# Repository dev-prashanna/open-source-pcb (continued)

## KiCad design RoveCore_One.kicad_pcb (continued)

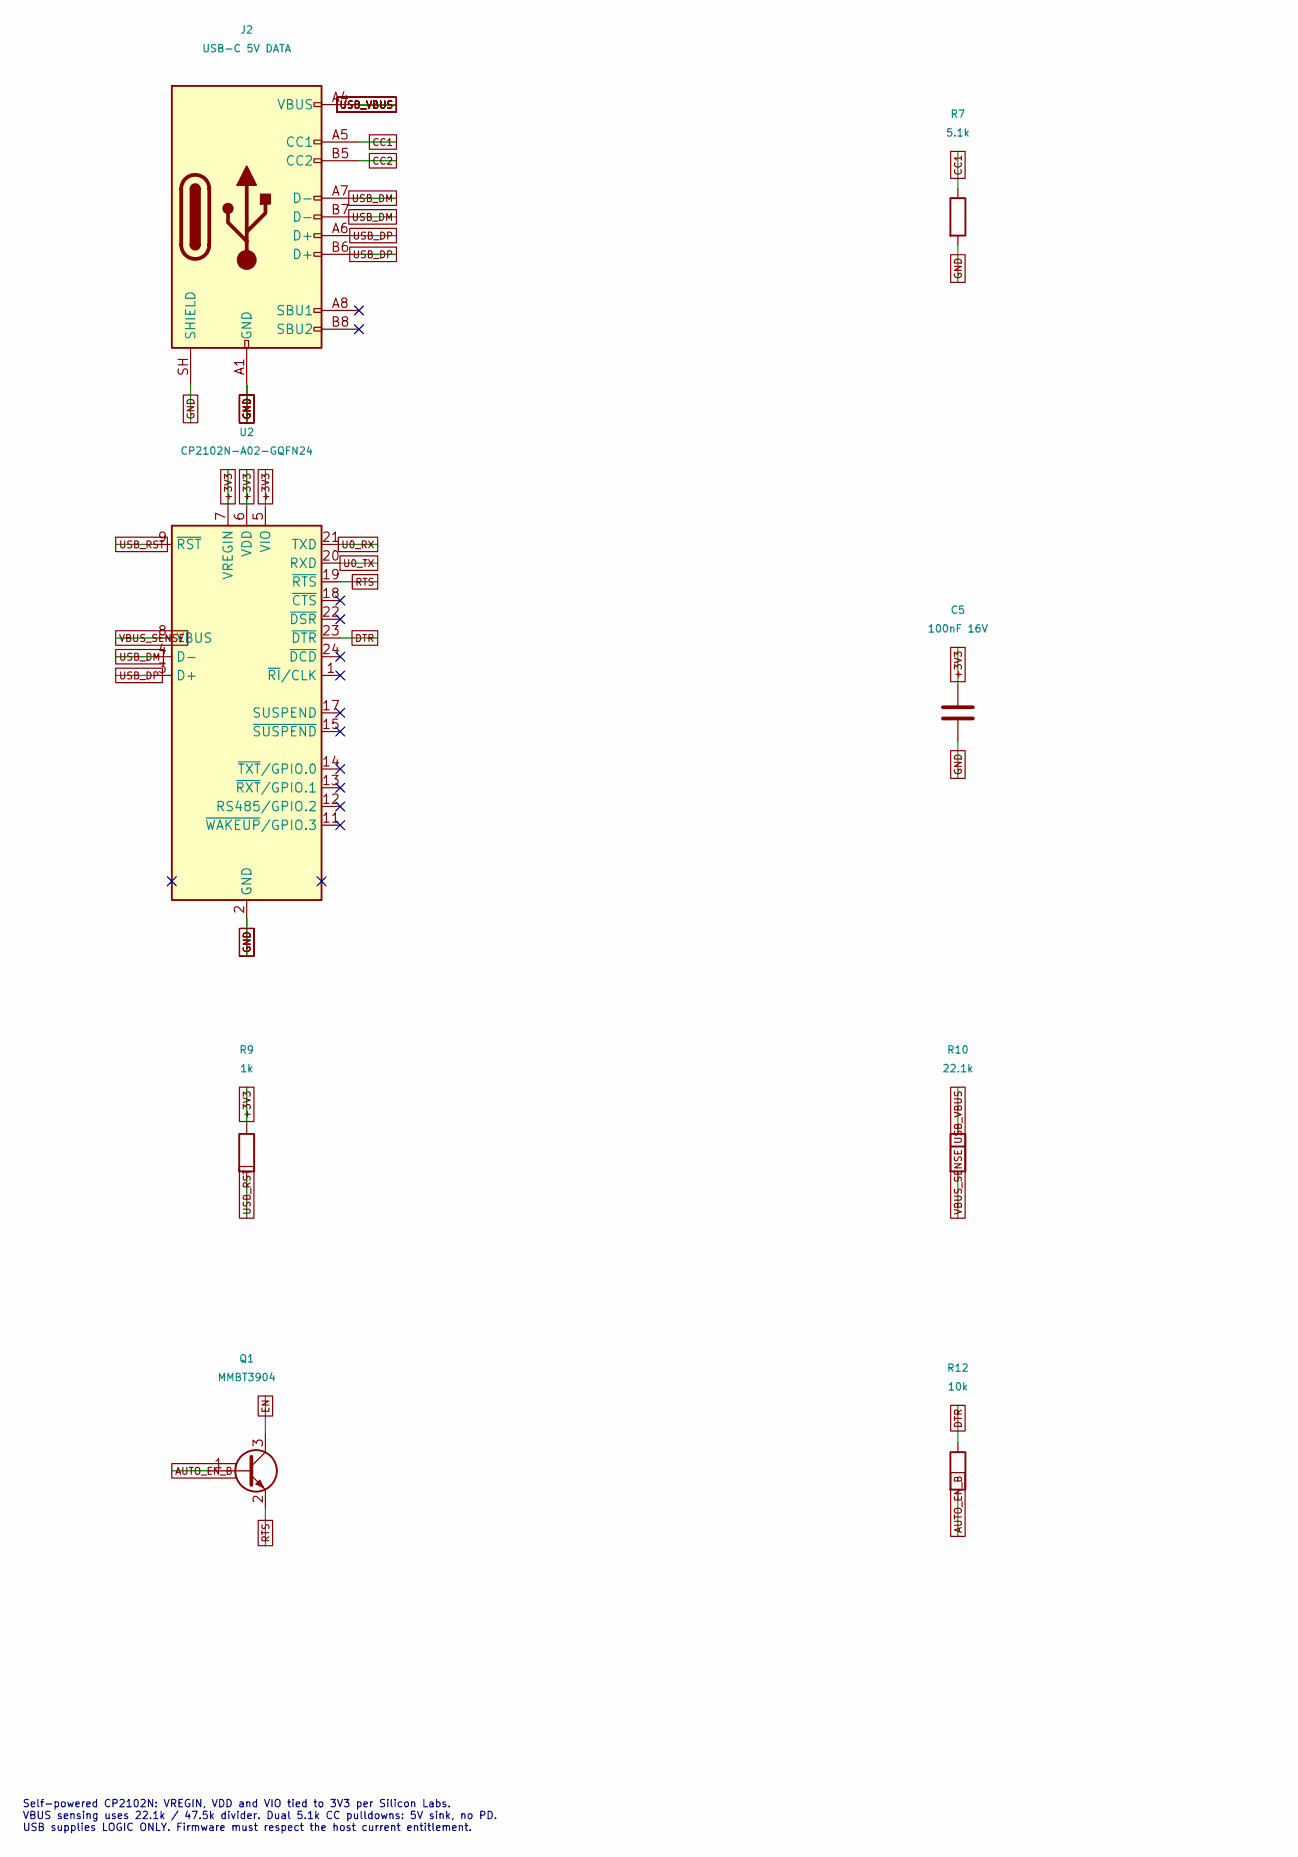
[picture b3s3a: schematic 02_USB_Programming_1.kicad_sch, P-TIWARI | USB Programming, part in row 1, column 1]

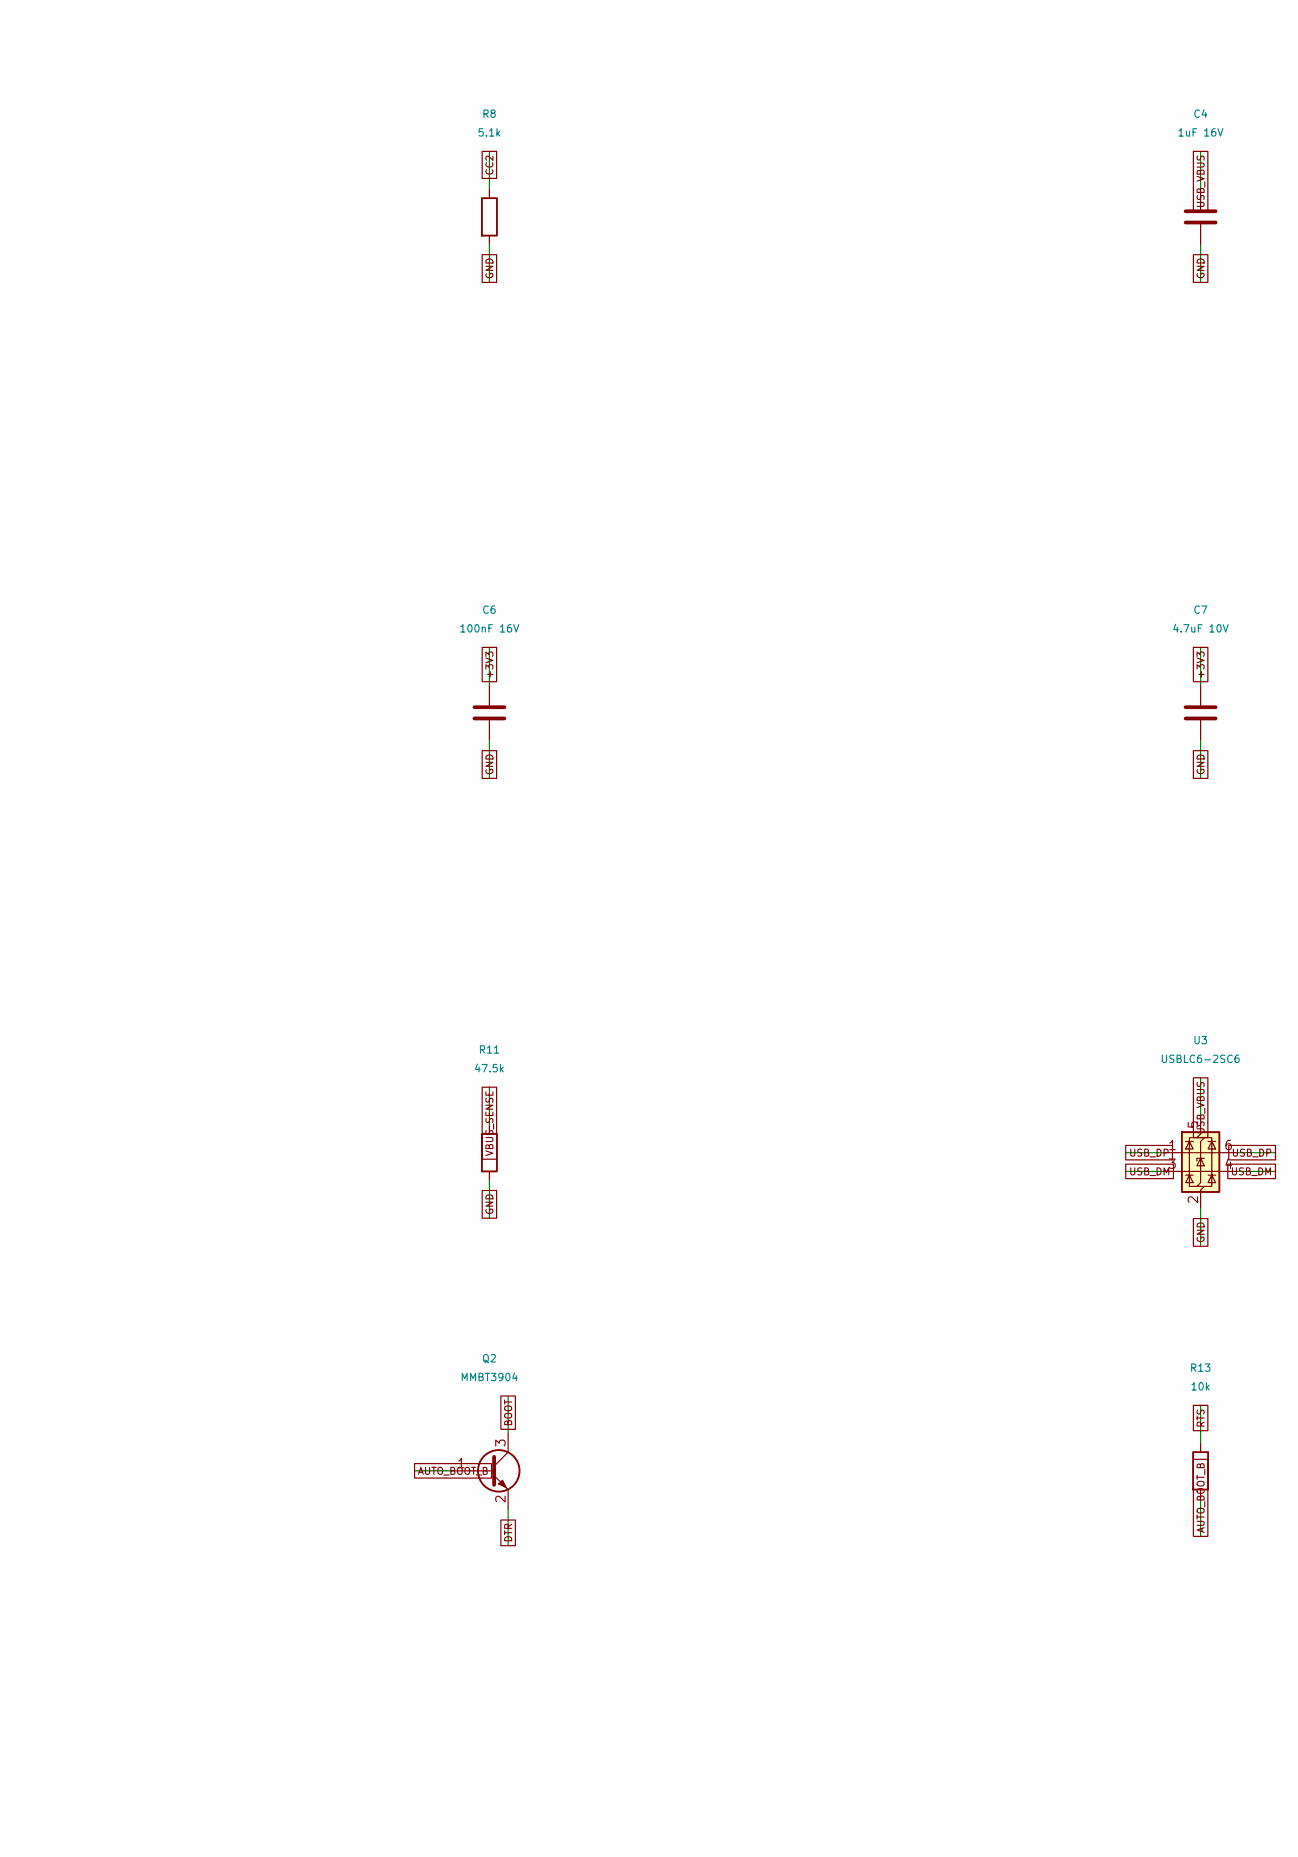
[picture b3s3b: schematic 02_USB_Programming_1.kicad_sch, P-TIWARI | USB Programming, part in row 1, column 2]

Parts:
C4: 1uF 16V; C_0603_1608Metric; MPN GRM188R61C105KA12D
C5, C6: 100nF 16V; C_0603_1608Metric; MPN GRM188R71C104KA01D
C7: 4.7uF 10V; C_0603_1608Metric; MPN GRM188R61A475KE15D
J2: USB-C 5V DATA; USB_C_Receptacle_HRO_TYPE-C-31-M-12; MPN TYPE-C-31-M-12
Q1, Q2: MMBT3904; SOT-23; MPN MMBT3904
R7, R8: 5.1k; R_0603_1608Metric; MPN RC0603FR-075K1L
R9: 1k; R_0603_1608Metric; MPN RC0603FR-071KL
R10: 22.1k; R_0603_1608Metric; MPN RC0603FR-0722K1L
R11: 47.5k; R_0603_1608Metric; MPN RC0603FR-0747K5L
R12, R13: 10k; R_0603_1608Metric; MPN RC0603FR-0710KL
U2: CP2102N-A02-GQFN24; QFN-24-1EP_4x4mm_P0.5mm_EP2.6x2.6mm; MPN CP2102N-A02-GQFN24
U3: USBLC6-2SC6; SOT-23-6; MPN USBLC6-2SC6

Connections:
+3V3: C5.1, C6.1, C7.1, R9.1, U2.5 (VIO), U2.6 (VDD), U2.7 (VREGIN); also elsewhere on the board
AUTO_BOOT_B: Q2.1 (B), R13.2
AUTO_EN_B: Q1.1 (B), R12.2
BOOT: Q2.3 (C); also elsewhere on the board
CC1: J2.A5 (CC1), R7.1
CC2: J2.B5 (CC2), R8.1
DTR: Q2.2 (E), R12.1, U2.23 (~DTR)
EN: Q1.3 (C); also elsewhere on the board
GND: C4.2, C5.2, C6.2, C7.2, J2.A1 (GND), J2.A12 (GND), J2.B1 (GND), J2.B12 (GND), J2.SH (SHIELD), R7.2, R8.2, R11.2, U2.2 (GND), U2.25 (GND), U3.2 (GND); also elsewhere on the board
RTS: Q1.2 (E), R13.1, U2.19 (~RTS)
U0_RX: U2.21 (TXD); also elsewhere on the board
U0_TX: U2.20 (RXD); also elsewhere on the board
USB_DM: J2.A7 (D-), J2.B7 (D-), U2.4 (D-), U3.3 (I/O2), U3.4 (I/O2)
USB_DP: J2.A6 (D+), J2.B6 (D+), U2.3 (D+), U3.1 (I/O1), U3.6 (I/O1)
USB_RST: R9.2, U2.9 (~RST)
USB_VBUS: C4.1, J2.A4 (VBUS), J2.A9 (VBUS), J2.B4 (VBUS), J2.B9 (VBUS), R10.1, U3.5 (VBUS); also elsewhere on the board
VBUS_SENSE: R10.2, R11.1, U2.8 (VBUS)

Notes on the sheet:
Self-powered CP2102N: VREGIN, VDD and VIO tied to 3V3 per Silicon Labs. VBUS sensing uses 22.1k / 47.5k divider. Dual 5.1k CC pulldowns: 5V sink, no PD. USB supplies LOGIC ONLY. Firmware must respect the host current entitlement.

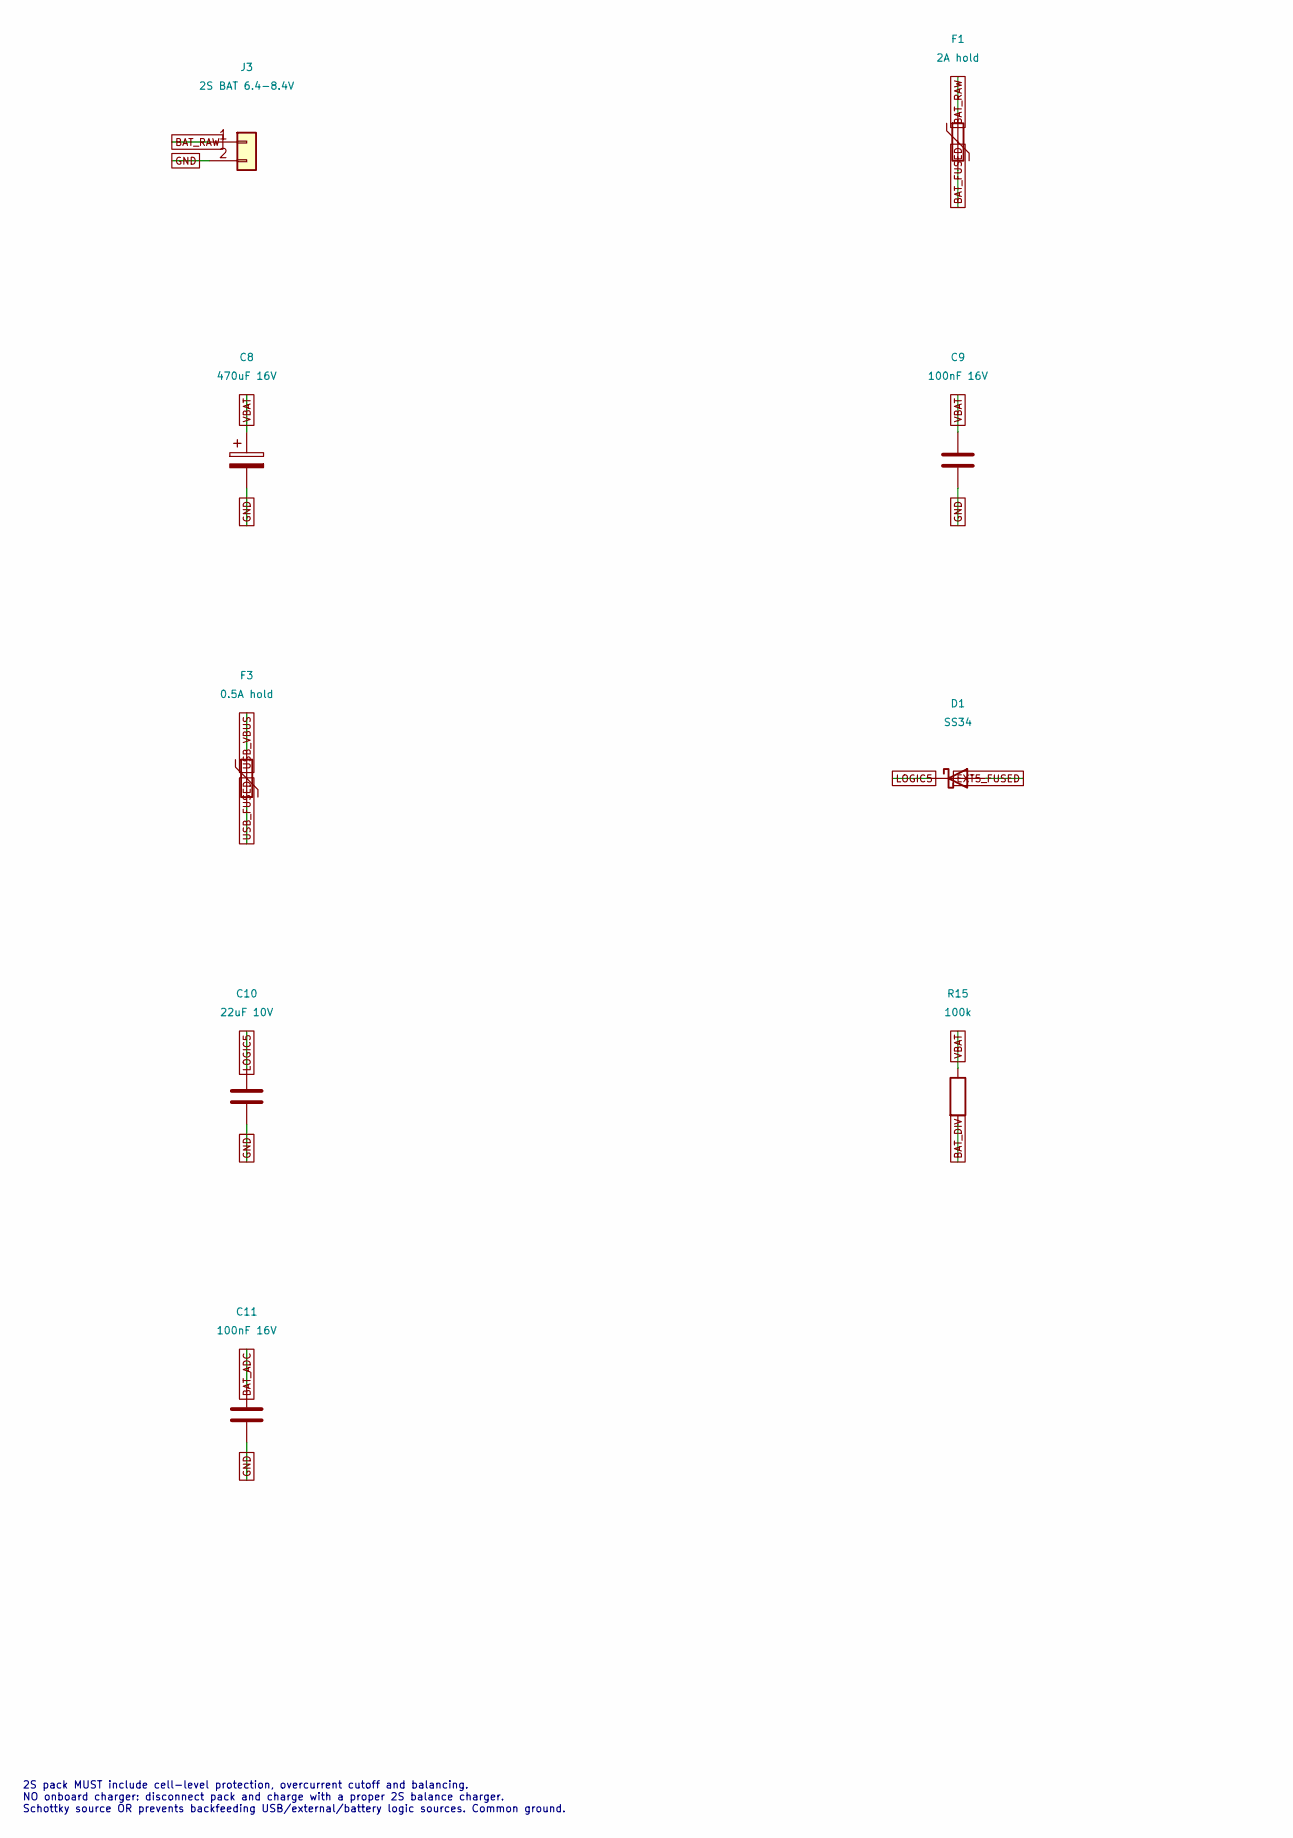
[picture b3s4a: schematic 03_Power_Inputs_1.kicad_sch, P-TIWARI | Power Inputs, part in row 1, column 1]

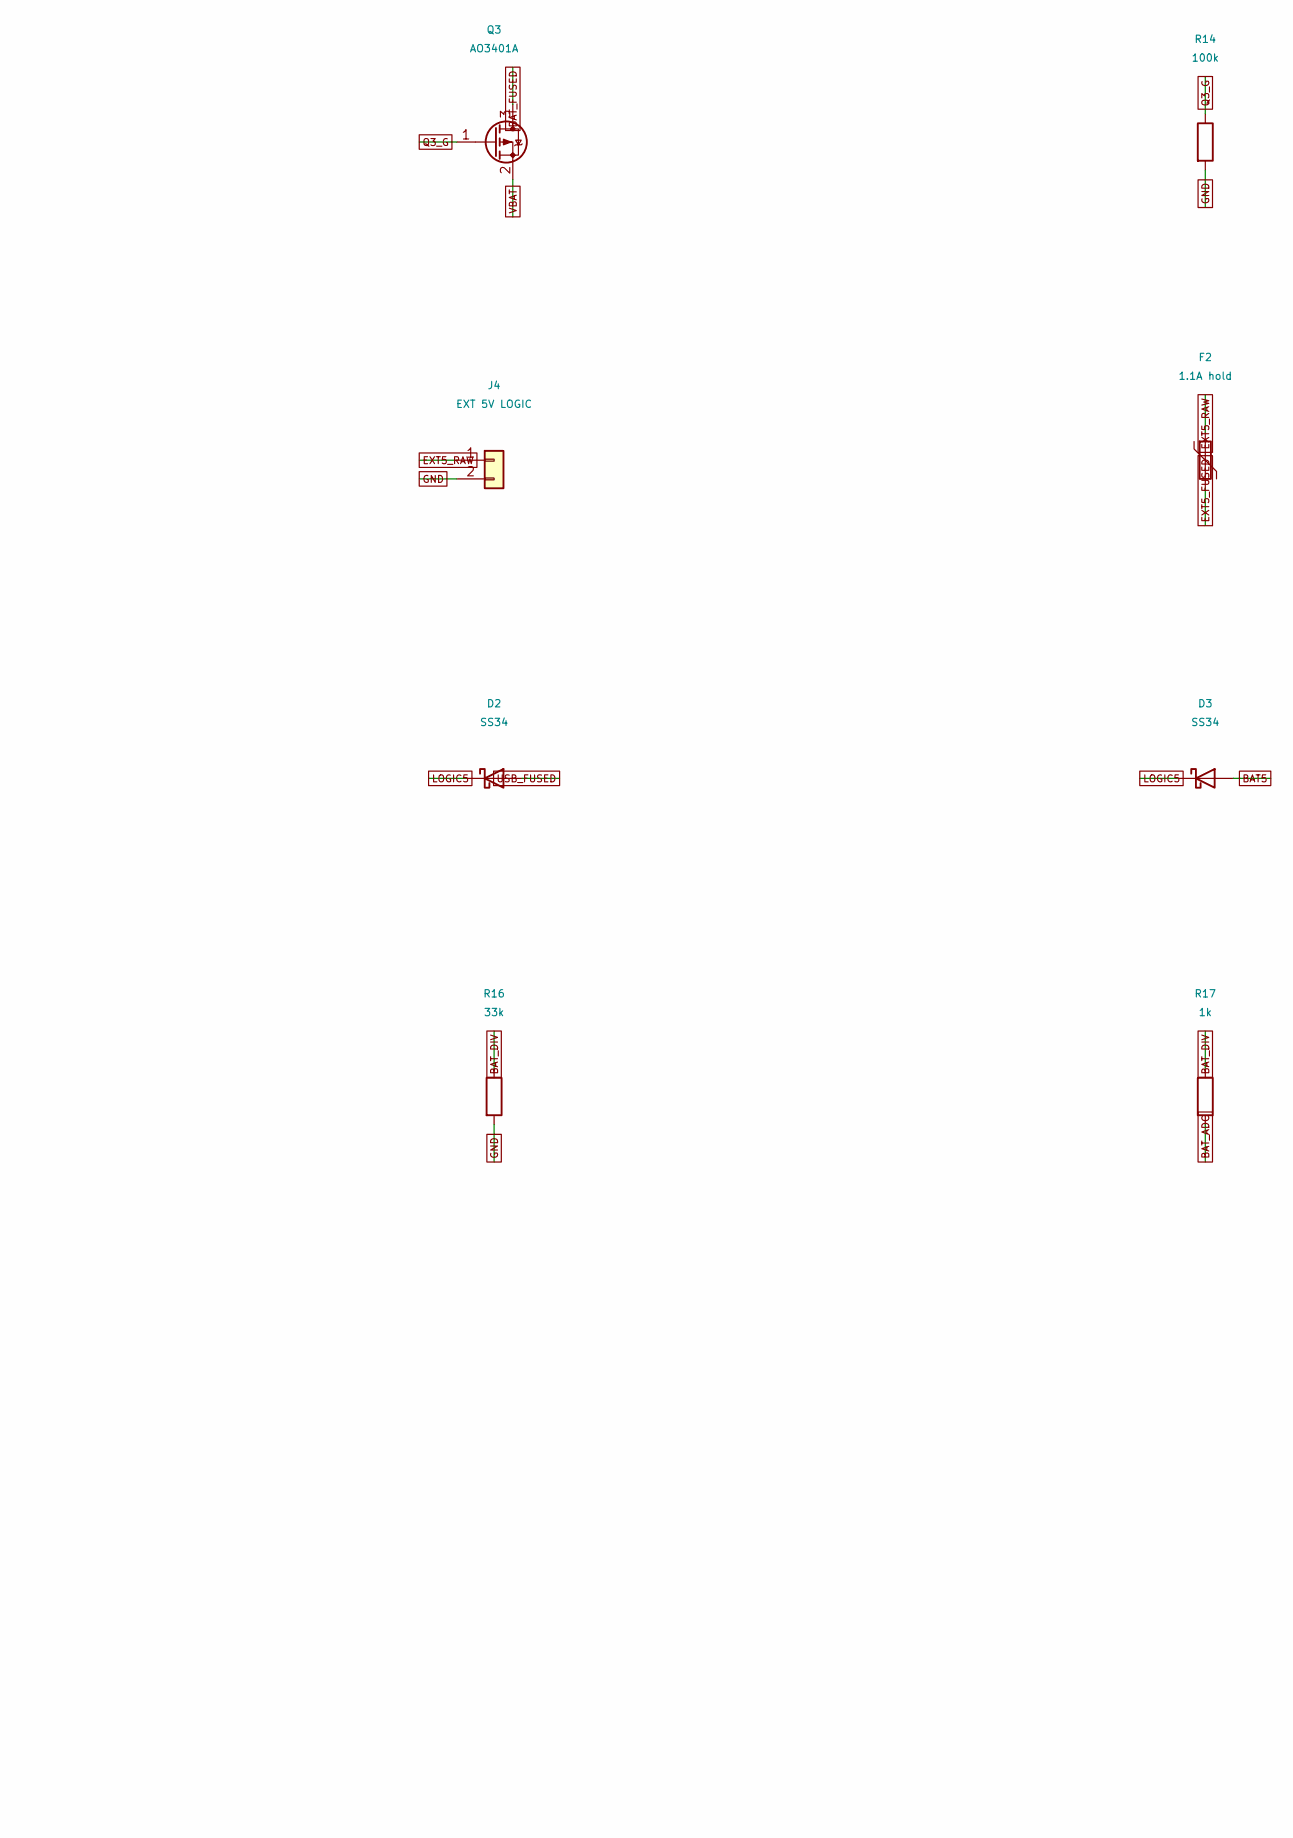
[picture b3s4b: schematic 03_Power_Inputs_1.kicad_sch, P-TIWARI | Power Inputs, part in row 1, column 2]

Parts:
C8: 470uF 16V; CP_Elec_8x10.5; MPN EEE-FK1C471P
C9, C11: 100nF 16V; C_0603_1608Metric; MPN GRM188R71C104KA01D
C10: 22uF 10V; C_0805_2012Metric; MPN GRM21BR61A226ME44L
D1, D2, D3: SS34; D_SMA; MPN SS34
F1: 2A hold; Fuse_1812_4532Metric; MPN 1812L200/16DR
F2: 1.1A hold; Fuse_1812_4532Metric; MPN 1812L110/16DR
F3: 0.5A hold; Fuse_1812_4532Metric; MPN 1812L050/24DR
J3: 2S BAT 6.4-8.4V; TerminalBlock_Phoenix_PT-1,5-2-3.5-H_1x02_P3.50mm_Horizontal; MPN 1984617
J4: EXT 5V LOGIC; TerminalBlock_Phoenix_PT-1,5-2-3.5-H_1x02_P3.50mm_Horizontal; MPN 1984617
Q3: AO3401A; SOT-23; MPN AO3401A
R14, R15: 100k; R_0603_1608Metric; MPN RC0603FR-07100KL
R16: 33k; R_0603_1608Metric; MPN RC0603FR-0733KL
R17: 1k; R_0603_1608Metric; MPN RC0603FR-071KL

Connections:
BAT5: D3.2 (A); also elsewhere on the board
BAT_ADC: C11.1, R17.2; also elsewhere on the board
BAT_DIV: R15.2, R16.1, R17.1
BAT_FUSED: F1.2, Q3.3 (D)
BAT_RAW: F1.1, J3.1
EXT5_FUSED: D1.2 (A), F2.2
EXT5_RAW: F2.1, J4.1
GND: C8.2, C9.2, C10.2, C11.2, J3.2, J4.2, R14.2, R16.2; also elsewhere on the board
LOGIC5: C10.1, D1.1 (K), D2.1 (K), D3.1 (K); also elsewhere on the board
Q3_G: Q3.1 (G), R14.1
USB_FUSED: D2.2 (A), F3.2
USB_VBUS: F3.1; also elsewhere on the board
VBAT: C8.1, C9.1, Q3.2 (S), R15.1; also elsewhere on the board

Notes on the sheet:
2S pack MUST include cell-level protection, overcurrent cutoff and balancing. NO onboard charger: disconnect pack and charge with a proper 2S balance charger. Schottky source OR prevents backfeeding USB/external/battery logic sources. Common ground.

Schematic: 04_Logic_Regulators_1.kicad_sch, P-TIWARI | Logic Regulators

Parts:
C12, C14, C17, C19: 100nF 16V; C_0603_1608Metric; MPN GRM188R71C104KA01D
C13, C18: 10uF 16V; C_0805_2012Metric; MPN GRM21BR61C106KE15L
C15, C16, C20, C21: 22uF 10V; C_0805_2012Metric; MPN GRM21BR61A226ME44L
C22: 4.7uF 10V; C_0603_1608Metric; MPN GRM188R61A475KE15D
FB1: 600R @100MHz; L_0603_1608Metric; MPN BLM18AG601SN1D
L1, L2: 4.7uH; L_Bourns_SRP5030T; MPN SRP5030T-4R7M
R18, R20, R21: 100k; R_0603_1608Metric; MPN RC0603FR-07100KL
R19: 27.4k; R_0603_1608Metric; MPN RC0603FR-0727K4L
U4: AP63205WU-7; TSOT-23-6; MPN AP63205WU-7
U5: AP63203WU-7; TSOT-23-6; MPN AP63203WU-7

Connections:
+3V3: C20.1, C21.1, FB1.1, L2.2, U5.1 (FB); also elsewhere on the board
+3V3_SENS: C22.1, FB1.2; also elsewhere on the board
BAT5: C15.1, C16.1, L1.2, U4.1 (FB); also elsewhere on the board
GND: C13.2, C14.2, C15.2, C16.2, C18.2, C19.2, C20.2, C21.2, C22.2, R19.2, R21.2, U4.4 (GND), U5.4 (GND); also elsewhere on the board
LOGIC5: C18.1, C19.1, R20.1, U5.3 (IN); also elsewhere on the board
SW_3V3: C17.2, L2.1, U5.5 (SW)
SW_BAT: C12.2, L1.1, U4.5 (SW)
U4_BST: C12.1, U4.6 (BST)
U4_EN: R18.2, R19.1, U4.2 (EN)
U5_BST: C17.1, U5.6 (BST)
U5_EN: R20.2, R21.1, U5.2 (EN)
VBAT: C13.1, C14.1, R18.1, U4.3 (IN); also elsewhere on the board

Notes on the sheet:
AP63205 battery buck 5V; AP63203 logic buck 3V3. Feedback on output side of inductors. Battery EN divider 100k/27.4k: nominal rising UVLO about 5.6V, NOT cell protection. 3V3 target 1A total, sensor/expansion budget 150mA. Quiet sensor branch uses ferrite + local caps.

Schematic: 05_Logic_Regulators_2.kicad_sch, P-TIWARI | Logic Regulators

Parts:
C23: 100nF 16V; C_0603_1608Metric; MPN GRM188R71C104KA01D
R22, R23: 2.2k; R_0603_1608Metric; MPN RC0603FR-072K2L

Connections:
+3V3: R22.1, R23.1; also elsewhere on the board
+3V3_SENS: C23.1; also elsewhere on the board
GND: C23.2; also elsewhere on the board
I2C_SCL: R23.2; also elsewhere on the board
I2C_SDA: R22.2; also elsewhere on the board

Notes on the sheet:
AP63205 battery buck 5V; AP63203 logic buck 3V3. Feedback on output side of inductors. Battery EN divider 100k/27.4k: nominal rising UVLO about 5.6V, NOT cell protection. 3V3 target 1A total, sensor/expansion budget 150mA. Quiet sensor branch uses ferrite + local caps.

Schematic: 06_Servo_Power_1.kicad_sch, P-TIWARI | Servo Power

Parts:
C24: 100nF 16V; C_0603_1608Metric; MPN GRM188R71C104KA01D
C25, C26: 10uF 16V; C_0805_2012Metric; MPN GRM21BR61C106KE15L
C27: 75pF 50V; C_0603_1608Metric; MPN GRM1885C1H750JA01D
C28, C29: 22uF 10V; C_0805_2012Metric; MPN GRM21BR61A226ME44L
C30: 470uF 16V; CP_Elec_8x10.5; MPN EEE-FK1C471P
F4: 2A hold; Fuse_1812_4532Metric; MPN 1812L200/16DR
J5: SERVO EXT 5-6V; TerminalBlock_Phoenix_PT-1,5-2-3.5-H_1x02_P3.50mm_Horizontal; MPN 1984617
JP1: SERVO SELECT 1-2 BAT / 2-3 EXT; PinHeader_1x03_P2.54mm_Vertical; MPN 61300311121
L3: 10uH; L_Bourns_SRP5030T; MPN SRP5030T-100M
Q4: AO3401A; SOT-23; MPN AO3401A
R24, R26, R28: 100k; R_0603_1608Metric; MPN RC0603FR-07100KL
R25: 27.4k; R_0603_1608Metric; MPN RC0603FR-0727K4L
R27: 13.3k; R_0603_1608Metric; MPN RC0603FR-0713K3L
U6: TPS54302DDCR; SOT-23-6; MPN TPS54302DDCR

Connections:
GND: C25.2, C26.2, C28.2, C29.2, C30.2, J5.2, R25.2, R27.2, R28.2, U6.1 (GND); also elsewhere on the board
Q4_G: Q4.1 (G), R28.1
SERVO5: C30.1, F4.2; also elsewhere on the board
SERVO_BOOT: C24.1, U6.6 (BOOT)
SERVO_BUCK: C27.1, C28.1, C29.1, JP1.1, L3.2, R26.1
SERVO_EN: R24.2, R25.1, U6.5 (EN)
SERVO_EXT: JP1.3, Q4.2 (S)
SERVO_EXT_RAW: J5.1, Q4.3 (D)
SERVO_FB: C27.2, R26.2, R27.1, U6.4 (FB)
SERVO_SELECTED: F4.1, JP1.2
SW_SERVO: C24.2, L3.1, U6.2 (SW)
VBAT: C25.1, C26.1, R24.1, U6.3 (VIN); also elsewhere on the board

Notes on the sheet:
Servo source selector: fit ONE shunt only. Never bridge both supplies. TPS54302 nominal Vout = 0.596*(1+100/13.3) = 5.077V. 10uH, 44uF ceramic, 75pF feedforward. Servo recommendation: 2A total continuous, 3A brief peak ONLY after thermal validation. Four small servos, not four stall currents.

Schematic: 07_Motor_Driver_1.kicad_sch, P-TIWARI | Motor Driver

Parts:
C31: 10nF 25V; C_0603_1608Metric; MPN GRM188R71E103KA01D
C32: 2.2uF 10V; C_0603_1608Metric; MPN GRM188R61A225KE34D
C33: 100nF 16V; C_0603_1608Metric; MPN GRM188R71C104KA01D
C34: 10uF 16V; C_0805_2012Metric; MPN GRM21BR61C106KE15L
C35: 470uF 16V; CP_Elec_8x10.5; MPN EEE-FK1C471P
F5: 2A hold; Fuse_1812_4532Metric; MPN 1812L200/16DR
J6: VM 3-8.4V; TerminalBlock_Phoenix_PT-1,5-2-3.5-H_1x02_P3.50mm_Horizontal; MPN 1984617
J7: MOTOR A; TerminalBlock_Phoenix_PT-1,5-2-3.5-H_1x02_P3.50mm_Horizontal; MPN 1984617
J8: MOTOR B; TerminalBlock_Phoenix_PT-1,5-2-3.5-H_1x02_P3.50mm_Horizontal; MPN 1984617
Q5: AO3401A; SOT-23; MPN AO3401A
R29, R32, R34, R35, R36, R37: 100k; R_0603_1608Metric; MPN RC0603FR-07100KL
R30, R31: 0.25R 1W; R_2512_6332Metric; MPN WSL2512R2500FEA
R33: 10k; R_0603_1608Metric; MPN RC0603FR-0710KL
U7: DRV8833PWPR; HTSSOP-16-1EP_4.4x5mm_P0.65mm_EP3.4x5mm_Mask2.46x2.31mm_The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; MPN DRV8833PWPR

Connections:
+3V3: R33.1; also elsewhere on the board
GND: C32.2, C33.2, C34.2, C35.2, J6.2, R29.2, R30.2, R31.2, R32.2, R34.2, R35.2, R36.2, R37.2, U7.13 (GND), U7.17 (GND); also elsewhere on the board
ISENSE_A: R30.1, U7.3 (AISEN)
ISENSE_B: R31.1, U7.6 (BISEN)
MOTOR_A_N: J7.2, U7.4 (AOUT2)
MOTOR_A_P: J7.1, U7.2 (AOUT1)
MOTOR_B_N: J8.2, U7.5 (BOUT2)
MOTOR_B_P: J8.1, U7.7 (BOUT1)
MOTOR_FUSED: F5.2, Q5.3 (D)
MOTOR_RAW: F5.1, J6.1
M_A1: R34.1, U7.16 (AIN1); also elsewhere on the board
M_A2: R35.1, U7.15 (AIN2); also elsewhere on the board
M_B1: R36.1, U7.9 (BIN1); also elsewhere on the board
M_B2: R37.1, U7.10 (BIN2); also elsewhere on the board
M_FAULT: R33.2, U7.8 (~FAULT); also elsewhere on the board
M_SLEEP: R32.1, U7.1 (~SLEEP); also elsewhere on the board
M_VCP: C31.1, U7.11 (VCP)
M_VINT: C32.1, U7.14 (VINT)
Q5_G: Q5.1 (G), R29.1
VM: C31.2, C33.1, C34.1, C35.1, Q5.2 (S), U7.12 (VM)

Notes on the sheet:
DRV8833PWPR (PowerPAD), not uncooled PW. Rsense=0.25ohm => Itrip typ 0.8A. Recommend <=0.6A continuous each; 3-8.4V motor input. Limit is per bridge, not advertised 2A. Regenerative braking raises VM; use a sink-capable battery supply. Validate VM stays <10.8V in operation, <12V absolute. Fit 100nF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

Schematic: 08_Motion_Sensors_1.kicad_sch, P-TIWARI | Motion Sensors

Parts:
C36, C37, C39, C40, C41: 100nF 16V; C_0603_1608Metric; MPN GRM188R71C104KA01D
C38: 1uF 16V; C_0603_1608Metric; MPN GRM188R61C105KA12D
C42: 4.7uF 10V; C_0603_1608Metric; MPN GRM188R61A475KE15D
U8: LSM6DS3TR-C; LGA-14_3x2.5mm_P0.5mm_LayoutBorder3x4y; MPN LSM6DS3TR-C
U9: LIS3MDLTR; LGA-12_2x2mm_P0.5mm; MPN LIS3MDLTR

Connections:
+3V3_SENS: C36.1, C37.1, C38.1, C39.1, C40.1, C42.1, U8.5 (VDDIO), U8.8 (VDD), U8.12 (CS), U9.5 (Vdd), U9.6 (Vdd_IO), U9.10 (~CS); also elsewhere on the board
GND: C36.2, C37.2, C38.2, C39.2, C40.2, C41.2, C42.2, U8.1 (SDO/SA0), U8.6 (GND), U8.7 (GND), U9.2 (GND), U9.3 (GND), U9.9 (SDO/SA1), U9.12 (GND); also elsewhere on the board
I2C_SCL: U8.13 (SCL), U9.1 (SCL/SPC); also elsewhere on the board
I2C_SDA: U8.14 (SDA), U9.11 (SDA/SDI/SDO); also elsewhere on the board
IMU_INT: U8.4 (INT1); also elsewhere on the board
MAG_C1: C41.1, U9.4 (C1)

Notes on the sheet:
LSM6DS3TR-C uses installed LSM6DS3 symbol: identical 14-pin mapping, 3x2.5mm LGA footprint. IMU I2C 0x6A (SA0=0), INT1 direct GPIO32. Magnetometer I2C 0x1C (SA1=0). LIS3MDL reserved pins 2/12 grounded; C1 100nF. IMU SDx/SCx/INT2 intentionally unused. Calibrate accelerometer, gyro bias and compass h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

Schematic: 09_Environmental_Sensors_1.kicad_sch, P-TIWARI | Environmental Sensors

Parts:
C43, C44, C45: 100nF 16V; C_0603_1608Metric; MPN GRM188R71C104KA01D
U10: BME280; Bosch_LGA-8_2.5x2.5mm_P0.65mm_ClockwisePinNumbering_Board; MPN BME280
U11: VEML7700-TT; VEML7700_TT; MPN VEML7700-TT

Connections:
+3V3_SENS: C43.1, C44.1, C45.1, U10.2 (CSB), U10.6 (VDDIO), U10.8 (VDD), U11.2 (VDD); also elsewhere on the board
GND: C43.2, C44.2, C45.2, U10.1 (GND), U10.5 (SDO), U10.7 (GND), U11.3 (GND); also elsewhere on the board
I2C_SCL: U10.4 (SCK), U11.1 (SCL); also elsewhere on the board
I2C_SDA: U10.3 (SDI), U11.4 (SDA); also elsewhere on the board

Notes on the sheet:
BME280 I2C 0x76; CSB=VDDIO, SDO=GND. VEML7700 fixed 0x10. Keep optical/pressure openings clear. Do not wash MEMS/optical sensors without supplier approval. BME temperature includes PCB self-heating; characterize board-on offsets under Wi-Fi/motor load.

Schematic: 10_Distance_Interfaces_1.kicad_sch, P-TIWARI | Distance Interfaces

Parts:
C46, C47, C49, C51: 100nF 16V; C_0603_1608Metric; MPN GRM188R71C104KA01D
C48: 4.7uF 10V; C_0603_1608Metric; MPN GRM188R61A475KE15D
C50: 100pF 50V; C_0603_1608Metric; MPN GRM1885C1H101JA01D
J9: ULTRASONIC 5V; JST_GH_SM04B-GHS-TB_1x04-1MP_P1.25mm_Horizontal; MPN SM04B-GHS-TB(LF)(SN)
R38, R39: 10k; R_0603_1608Metric; MPN RC0603FR-0710KL
R40: 1k; R_0603_1608Metric; MPN RC0603FR-071KL
R41: 100k; R_0603_1608Metric; MPN RC0603FR-07100KL
U12: VL53L1CXV0FY1; ST_VL53L1x; MPN VL53L1CXV0FY1
U13: SN74LVC1G17DBVR; SOT-23-5; MPN SN74LVC1G17DBVR

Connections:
+3V3: C49.1, U13.5 (VCC); also elsewhere on the board
+3V3_SENS: C46.1, C47.1, C48.1, R38.1, R39.1, U12.1 (AVDDVCSEL), U12.11 (AVDD); also elsewhere on the board
BAT5: C51.1, J9.1; also elsewhere on the board
GND: C46.2, C47.2, C48.2, C49.2, C50.2, C51.2, J9.4, R41.2, U12.2 (AVSSVCSEL), U12.3 (GND), U12.4 (GND), U12.6 (GND), U12.12 (GND), U13.3 (GND); also elsewhere on the board
I2C_SCL: U12.10 (SCL); also elsewhere on the board
I2C_SDA: U12.9 (SDA); also elsewhere on the board
TOF_INT: R39.2, U12.7 (GPIO1); also elsewhere on the board
TOF_XSHUT: R38.2, U12.5 (XSHUT); also elsewhere on the board
US_ECHO: U13.4; also elsewhere on the board
US_ECHO_RAW: J9.3, R40.1
US_ECHO_RC: C50.1, R40.2, R41.1, U13.2
US_TRIG5: J9.2; also elsewhere on the board

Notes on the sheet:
VL53L1X at 0x29: AVDD=3V3_SENS; program 2V8 IO mode with ST driver. XSHUT open-drain control only. DNC pin8 intentionally open. Aperture faces upward: mount board to suit sensing direction. Ultrasonic VCC is battery-derived BAT5: USB-only operation does not power 5V accessories. Echo uses 5.5V-tole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

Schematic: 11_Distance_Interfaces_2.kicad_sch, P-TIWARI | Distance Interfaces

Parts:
U14: SN74AHCT125PWR; TSSOP-14_4.4x5mm_P0.65mm; MPN SN74AHCT125PWR

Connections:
BAT5: U14.14 (VCC); also elsewhere on the board
GND: U14.1, U14.7 (GND); also elsewhere on the board
SERVO_OE: U14.4, U14.10, U14.13; also elsewhere on the board
SERVO_PWM0: U14.5; also elsewhere on the board
SERVO_PWM1: U14.9; also elsewhere on the board
SERVO_PWM2: U14.12; also elsewhere on the board
SERVO_SIG0: U14.6; also elsewhere on the board
SERVO_SIG1: U14.8; also elsewhere on the board
SERVO_SIG2: U14.11; also elsewhere on the board
US_TRIG: U14.2; also elsewhere on the board
US_TRIG5: U14.3; also elsewhere on the board

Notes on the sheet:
VL53L1X at 0x29: AVDD=3V3_SENS; program 2V8 IO mode with ST driver. XSHUT open-drain control only. DNC pin8 intentionally open. Aperture faces upward: mount board to suit sensing direction. Ultrasonic VCC is battery-derived BAT5: USB-only operation does not power 5V accessories. Echo uses 5.5V-tole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

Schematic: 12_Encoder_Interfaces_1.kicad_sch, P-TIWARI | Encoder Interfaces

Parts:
C52, C54, C56, C58: 100nF 16V; C_0603_1608Metric; MPN GRM188R71C104KA01D
C53, C55, C57: 100pF 50V; C_0603_1608Metric; MPN GRM1885C1H101JA01D
J10: ENC LEFT; JST_GH_SM04B-GHS-TB_1x04-1MP_P1.25mm_Horizontal; MPN SM04B-GHS-TB(LF)(SN)
J11: ENC RIGHT; JST_GH_SM04B-GHS-TB_1x04-1MP_P1.25mm_Horizontal; MPN SM04B-GHS-TB(LF)(SN)
R42, R44, R46, R48: 1k; R_0603_1608Metric; MPN RC0603FR-071KL
R43, R45, R47: 10k; R_0603_1608Metric; MPN RC0603FR-0710KL
U15, U16, U17, U18: SN74LVC1G17DBVR; SOT-23-5; MPN SN74LVC1G17DBVR

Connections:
+3V3: C52.1, C54.1, C56.1, C58.1, J10.1, J11.1, R43.1, R45.1, R47.1, U15.5 (VCC), U16.5 (VCC), U17.5 (VCC), U18.5 (VCC); also elsewhere on the board
ENC_LA: U15.4; also elsewhere on the board
ENC_LA_RAW: J10.3, R42.1, R43.2
ENC_LA_RAW_RC: C53.1, R42.2, U15.2
ENC_LB: U16.4; also elsewhere on the board
ENC_LB_RAW: J10.4, R44.1, R45.2
ENC_LB_RAW_RC: C55.1, R44.2, U16.2
ENC_RA: U17.4; also elsewhere on the board
ENC_RA_RAW: J11.3, R46.1, R47.2
ENC_RA_RAW_RC: C57.1, R46.2, U17.2
ENC_RB: U18.4; also elsewhere on the board
ENC_RB_RAW: J11.4, R48.1; also elsewhere on the board
ENC_RB_RAW_RC: R48.2, U18.2; also elsewhere on the board
GND: C52.2, C53.2, C54.2, C55.2, C56.2, C57.2, C58.2, J10.2, J11.2, U15.3 (GND), U16.3 (GND), U17.3 (GND), U18.3 (GND); also elsewhere on the board

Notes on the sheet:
Encoder connectors supply 3V3; push-pull or open-collector inputs accepted. A/B inputs buffer-rated 0-5.5V, with 1k/100pF RC (~100ns) and 10k pullups. GPIO36/39 left, GPIO34/35 right. Use ESP32 PCNT; no reliance on missing internal pullups. External 5V encoder supply allowed only with shared ground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

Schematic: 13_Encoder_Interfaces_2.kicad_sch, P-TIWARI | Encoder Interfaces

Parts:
C59: 100pF 50V; C_0603_1608Metric; MPN GRM1885C1H101JA01D
R49: 10k; R_0603_1608Metric; MPN RC0603FR-0710KL

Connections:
+3V3: R49.1; also elsewhere on the board
ENC_RB_RAW: R49.2; also elsewhere on the board
ENC_RB_RAW_RC: C59.1; also elsewhere on the board
GND: C59.2; also elsewhere on the board

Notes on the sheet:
Encoder connectors supply 3V3; push-pull or open-collector inputs accepted. A/B inputs buffer-rated 0-5.5V, with 1k/100pF RC (~100ns) and 10k pullups. GPIO36/39 left, GPIO34/35 right. Use ESP32 PCNT; no reliance on missing internal pullups. External 5V encoder supply allowed only with shared ground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

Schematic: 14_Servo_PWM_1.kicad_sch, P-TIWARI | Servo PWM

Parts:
C60, C61: 100nF 16V; C_0603_1608Metric; MPN GRM188R71C104KA01D
J12: SERVO 1; PinHeader_1x03_P2.54mm_Vertical; MPN 61300311121
J13: SERVO 2; PinHeader_1x03_P2.54mm_Vertical; MPN 61300311121
J14: SERVO 3; PinHeader_1x03_P2.54mm_Vertical; MPN 61300311121
J15: SERVO 4; PinHeader_1x03_P2.54mm_Vertical; MPN 61300311121
R50, R52, R54, R56: 220; R_0603_1608Metric; MPN RC0603FR-07220RL
R51, R53, R55, R57: 100k; R_0603_1608Metric; MPN RC0603FR-07100KL
U19: PCA9685PW,118; TSSOP-28_4.4x9.7mm_P0.65mm; MPN PCA9685PW,118
U20: SN74AHCT1G125DBVR; SOT-23-5_Board; MPN SN74AHCT1G125DBVR

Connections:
+3V3: C60.1, U19.28 (VDD); also elsewhere on the board
BAT5: C61.1, U20.5 (VCC); also elsewhere on the board
GND: C60.2, C61.2, J12.1, J13.1, J14.1, J15.1, R51.2, R53.2, R55.2, R57.2, U19.1 (A0), U19.2 (A1), U19.3 (A2), U19.4 (A3), U19.5 (A4), U19.14 (VSS), U19.24 (A5), U19.25 (EXTCLK), U20.3 (GND); also elsewhere on the board
I2C_SCL: U19.26 (SCL); also elsewhere on the board
I2C_SDA: U19.27 (SDA); also elsewhere on the board
SERVO5: J12.2, J13.2, J14.2, J15.2; also elsewhere on the board
SERVO_OE: U19.23 (~OE), U20.1; also elsewhere on the board
SERVO_OUT0: J12.3, R50.2, R51.1
SERVO_OUT1: J13.3, R52.2, R53.1
SERVO_OUT2: J14.3, R54.2, R55.1
SERVO_OUT3: J15.3, R56.2, R57.1
SERVO_PWM0: U19.6 (LED0); also elsewhere on the board
SERVO_PWM1: U19.7 (LED1); also elsewhere on the board
SERVO_PWM2: U19.8 (LED2); also elsewhere on the board
SERVO_PWM3: U19.9 (LED3), U20.2
SERVO_SIG0: R50.1; also elsewhere on the board
SERVO_SIG1: R52.1; also elsewhere on the board
SERVO_SIG2: R54.1; also elsewhere on the board
SERVO_SIG3: R56.1, U20.4

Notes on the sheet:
PCA9685 0x40; default all-call 0x70, disable if conflicting extension is installed. GPIO15 high disables AHCT output buffers and PCA9685. Set low only after setting valid 50Hz pulses. Each servo: GND / servo rail / 5V PWM. Servo supply and BAT5 logic are distinct. Unused PWM channels intentionally 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

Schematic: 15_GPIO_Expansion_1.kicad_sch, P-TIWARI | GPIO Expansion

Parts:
C62: 100nF 16V; C_0603_1608Metric; MPN GRM188R71C104KA01D
J16: I2C 3V3; JST_GH_SM04B-GHS-TB_1x04-1MP_P1.25mm_Horizontal; MPN SM04B-GHS-TB(LF)(SN)
J17: SPI / LORA; JST_GH_SM06B-GHS-TB_1x06-1MP_P1.25mm_Horizontal; MPN SM06B-GHS-TB(LF)(SN)
J18: GPS / UART; JST_GH_SM04B-GHS-TB_1x04-1MP_P1.25mm_Horizontal; MPN SM04B-GHS-TB(LF)(SN)
J19: GPIO EXP 3V3; PinHeader_1x10_P2.00mm_Vertical; MPN M22-2011005
J20: ESP GPIO SHARED; PinHeader_1x10_P2.00mm_Vertical; MPN M22-2011005
J21: ESP GPIO INPUTS; PinHeader_1x08_P2.00mm_Vertical; MPN M22-2010805
TP1: EXP_B0; ServicePad_0.5mm; MPN PCB copper feature
TP2: EXP_B1; ServicePad_0.5mm; MPN PCB copper feature
TP3: EXP_B2; ServicePad_0.5mm; MPN PCB copper feature
U21: MCP23017-E/SS; SSOP-28_5.3x10.2mm_P0.65mm; MPN MCP23017-E/SS

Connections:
+3V3: C62.1, J16.1, J17.2, J18.2, J19.2, J20.2, U21.9 (V_{DD}); also elsewhere on the board
BAT_ADC: J20.8; also elsewhere on the board
BUZZ_PWM: J21.3; also elsewhere on the board
EN: U21.18 (~RESET); also elsewhere on the board
ENC_LA: J21.4; also elsewhere on the board
ENC_LB: J21.5; also elsewhere on the board
ENC_RA: J21.6; also elsewhere on the board
ENC_RB: J21.7; also elsewhere on the board
EXP_B0: TP1.1, U21.1 (GPB0)
EXP_B1: TP2.1, U21.2 (GPB1)
EXP_B2: TP3.1, U21.3 (GPB2)
EXP_B3: J19.6, U21.4 (GPB3)
EXP_B4: J19.7, U21.5 (GPB4)
EXP_B5: J19.8, U21.6 (GPB5)
EXP_B6: J19.9, U21.7 (GPB6)
EXP_B7: J19.10, U21.8 (GPB7); also elsewhere on the board
GND: C62.2, J16.2, J17.1, J18.1, J19.1, J19.3, J19.4, J19.5, J20.1, J21.1, U21.10 (V_{SS}), U21.15 (A0), U21.16 (A1), U21.17 (A2); also elsewhere on the board
I2C_SCL: J16.4, U21.12 (SCK); also elsewhere on the board
I2C_SDA: J16.3, U21.13 (SDA); also elsewhere on the board
IMU_INT: J20.7; also elsewhere on the board
M_A1: J20.3; also elsewhere on the board
M_A2: J20.4; also elsewhere on the board
M_B1: J20.5; also elsewhere on the board
M_B2: J20.6; also elsewhere on the board
M_FAULT: U21.22 (GPA1); also elsewhere on the board
M_SLEEP: U21.21 (GPA0); also elsewhere on the board
RGB_B: U21.28 (GPA7); also elsewhere on the board
RGB_G: U21.27 (GPA6); also elsewhere on the board
RGB_R: U21.26 (GPA5); also elsewhere on the board
SERVO_OE: J21.2; also elsewhere on the board
SPI_CS: J17.6, J21.8; also elsewhere on the board
SPI_MISO: J17.5; also elsewhere on the board
SPI_MOSI: J17.4; also elsewhere on the board
SPI_SCK: J17.3; also elsewhere on the board
TOF_INT: U21.24 (GPA3); also elsewhere on the board
TOF_XSHUT: U21.23 (GPA2); also elsewhere on the board
UART_RX: J18.4; also elsewhere on the board
UART_TX: J18.3; also elsewhere on the board
USER_BTN: U21.25 (GPA4); also elsewhere on the board
US_ECHO: J20.10; also elsewhere on the board
US_TRIG: J20.9; also elsewhere on the board

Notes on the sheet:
MCP23017 fixed 0x20. GPA0 sleep defaults LOW by external resistor; all pins reset as inputs. GPA2 must be open-drain emulated: output LOW for shutdown, input for release; never drive HIGH. GPB0..7 expansion are 3V3 GPIO; GPB7 also drives onboard load MOSFET. GPIO headers expose SHARED nets: disable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

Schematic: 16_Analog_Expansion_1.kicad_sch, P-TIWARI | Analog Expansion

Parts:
C63: 100nF 16V; C_0603_1608Metric; MPN GRM188R71C104KA01D
C64, C65, C66, C67: 10nF 25V; C_0603_1608Metric; MPN GRM188R71E103KA01D
D10, D11, D12, D13: BAT54S; SOT-23; MPN BAT54S-7-F
J22: ANALOG 0-3V3; JST_GH_SM06B-GHS-TB_1x06-1MP_P1.25mm_Horizontal; MPN SM06B-GHS-TB(LF)(SN)
R58, R59, R60, R61: 4.7k; R_0603_1608Metric; MPN RC0603FR-074K7L
U22: ADS1115IDGSR; TSSOP-10_3x3mm_P0.5mm; MPN ADS1115IDGSR

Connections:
+3V3: J22.1; also elsewhere on the board
+3V3_SENS: C63.1, D10.2 (K), D11.2 (K), D12.2 (K), D13.2 (K), U22.8 (VDD); also elsewhere on the board
AN0: C64.1, D10.3 (COM), R58.2, U22.4 (AIN0)
AN1: C65.1, D11.3 (COM), R59.2, U22.5 (AIN1)
AN2: C66.1, D12.3 (COM), R60.2, U22.6 (AIN2)
AN3: C67.1, D13.3 (COM), R61.2, U22.7 (AIN3)
AN_IN0: J22.3, R58.1
AN_IN1: J22.4, R59.1
AN_IN2: J22.5, R60.1
AN_IN3: J22.6, R61.1
GND: C63.2, C64.2, C65.2, C66.2, C67.2, D10.1 (A), D11.1 (A), D12.1 (A), D13.1 (A), J22.2, U22.1 (ADDR), U22.3 (GND); also elsewhere on the board
I2C_SCL: U22.10 (SCL); also elsewhere on the board
I2C_SDA: U22.9 (SDA); also elsewhere on the board

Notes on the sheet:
ADS1115 address 0x48, 860 samples/s aggregate maximum. Choose PGA +/-4.096V. Input voltage range remains 0..3.3V; PGA range is NOT input tolerance. 4.7k / 10nF filtering with Schottky clamps. Suitable for analog line sensor array. 4 channels sequentially sampled; high-speed line control may need an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
